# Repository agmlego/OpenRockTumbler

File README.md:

OpenRockTumbler
---------------

This project aims to be a drop-in replacement controller for common rock tumblers such as the KoolStone C1 Pro.

# Goals

* ESPHome-compatible controller for potential integration with Home Assistant
* Timer:
  * More than 9-day limit
  * Resume tumbling after power loss if time remaining
  * Periodic stir operation after timer end to prevent grit from settling
* Hall effect rotation sensor:
  * Detect if drum is actually turning
    * Alerts if belt breaks
  * Constant speed control

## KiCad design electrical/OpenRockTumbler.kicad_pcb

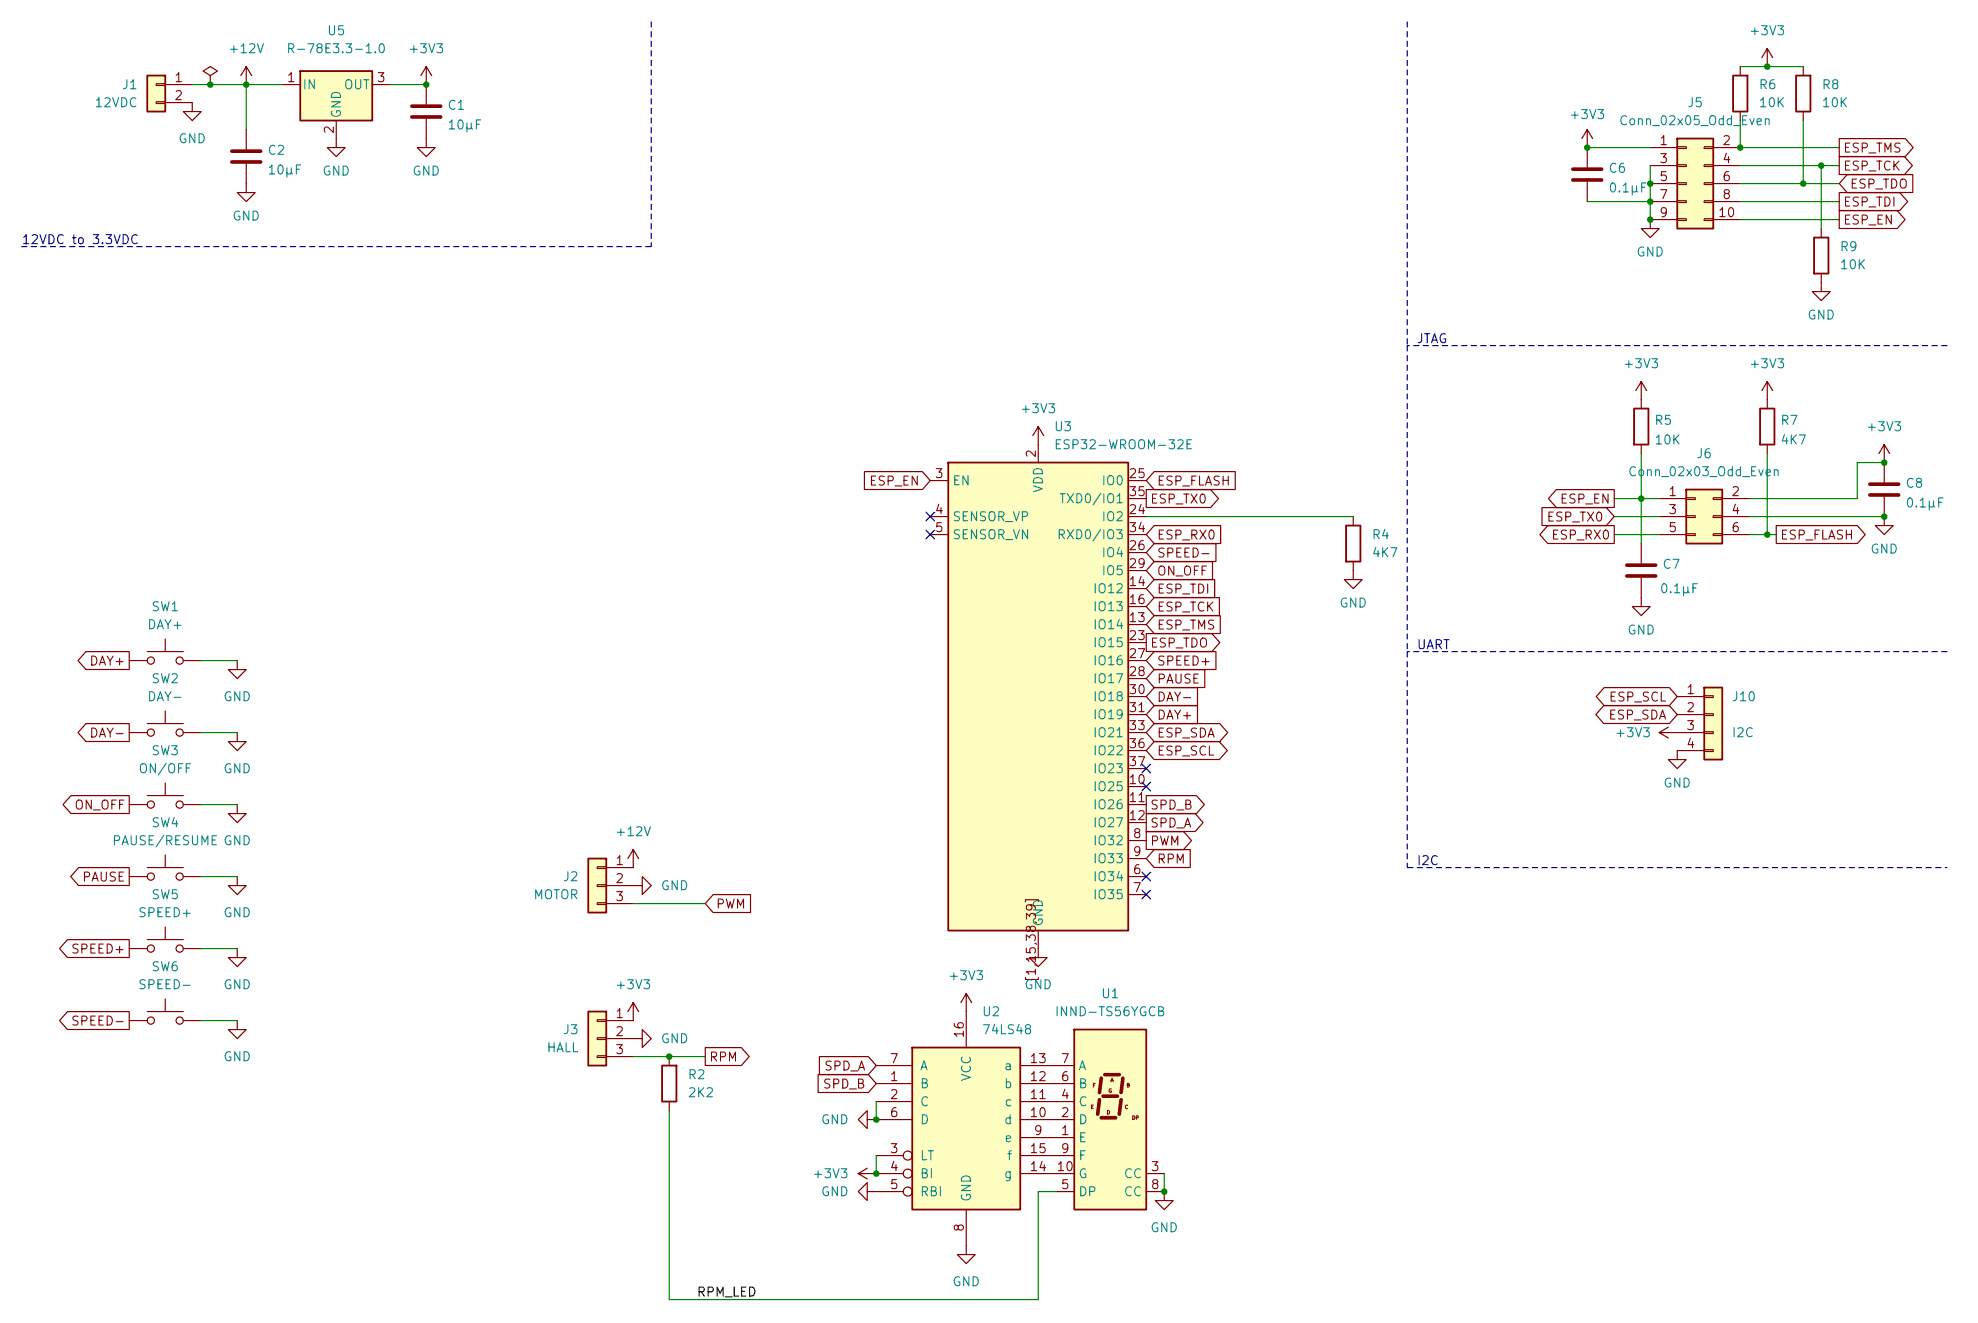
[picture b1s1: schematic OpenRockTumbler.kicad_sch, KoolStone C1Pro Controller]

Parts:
C1, C2: 10µF; CP_Elec_4x4.5
C6, C7, C8: 0.1µF; C_0603_1608Metric
J1: 12VDC; JST_PH_S2B-PH-K_1x02_P2.00mm_Horizontal
J2: MOTOR; JST_PH_S3B-PH-K_1x03_P2.00mm_Horizontal
J3: HALL; JST_PH_S3B-PH-K_1x03_P2.00mm_Horizontal
J5: Conn_02x05_Odd_Even; Tag-Connect_TC2050-IDC-NL_2x05_P1.27mm_Vertical
J6: Conn_02x03_Odd_Even; Tag-Connect_TC2030-IDC-NL_2x03_P1.27mm_Vertical
J10: I2C; JST_PH_S4B-PH-K_1x04_P2.00mm_Horizontal
R2: 2K2; R_0603_1608Metric
R4, R7: 4K7; R_0603_1608Metric
R5, R6, R8, R9: 10K; R_0603_1608Metric
SW1: DAY+; SW_PUSH_6mm
SW2: DAY-; SW_PUSH_6mm
SW3: ON/OFF; SW_PUSH_6mm
SW4: PAUSE/RESUME; SW_PUSH_6mm
SW5: SPEED+; SW_PUSH_6mm
SW6: SPEED-; SW_PUSH_6mm
U1: INND-TS56YGCB; D1X8K
U2: 74LS48; SOIC-16_3.9x9.9mm_P1.27mm
U3: ESP32-WROOM-32E
U5: R-78E3.3-1.0; Converter_DCDC_RECOM_R-78E-0.5_THT

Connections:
+3V3: C1.1, C6.1, C8.1, J3.1, J5.1, J6.2, J10.3, R5.1, R6.2, R7.1, R8.2, U2.3 (LT), U2.4 (BI), U2.16 (VCC), U3.2 (VDD), U5.3 (OUT)
+12V: C2.1, J1.1, J2.1, U5.1 (IN)
/RPM_LED: R2.1, U1.5 (DP)
DAY+: SW1.1, U3.31 (IO19)
DAY-: SW2.1, U3.30 (IO18)
ESP_EN: C7.1, J5.10, J6.1, R5.2, U3.3 (EN)
ESP_FLASH: J6.6, R7.2, U3.25 (IO0)
ESP_RX0: J6.5, U3.34 (RXD0/IO3)
ESP_SCL: J10.1, U3.36 (IO22)
ESP_SDA: J10.2, U3.33 (IO21)
ESP_TCK: J5.4, R9.1, U3.16 (IO13)
ESP_TDI: J5.8, U3.14 (IO12)
ESP_TDO: J5.6, R8.1, U3.23 (IO15)
ESP_TMS: J5.2, R6.1, U3.13 (IO14)
ESP_TX0: J6.3, U3.35 (TXD0/IO1)
GND: C1.2, C2.2, C6.2, C7.2, C8.2, J1.2, J2.2, J3.2, J5.3, J5.5, J5.7, J5.9, J6.4, J10.4, R4.2, R9.2, SW1.2, SW2.2, SW3.2, SW4.2, SW5.2, SW6.2, U1.3 (CC), U1.8 (CC), U2.2 (C), U2.5 (RBI), U2.6 (D), U2.8 (GND), U3.1 (GND), U3.15 (GND), U3.38 (GND), U3.39 (GND), U3.[1,15,38,39] (GND), U5.2 (GND)
unnamed: U1.7 (A), U2.13 (a)
unnamed: U1.6 (B), U2.12 (b)
unnamed: U1.4 (C), U2.11 (c)
unnamed: U1.2 (D), U2.10 (d)
unnamed: U1.1 (E), U2.9 (e)
unnamed: U1.9 (F), U2.15 (f)
unnamed: U1.10 (G), U2.14 (g)
unnamed: R4.1, U3.24 (IO2)
ON_OFF: SW3.1, U3.29 (IO5)
PAUSE: SW4.1, U3.28 (IO17)
PWM: J2.3, U3.8 (IO32)
RPM: J3.3, R2.2, U3.9 (IO33)
SPD_A: U2.7 (A), U3.12 (IO27)
SPD_B: U2.1 (B), U3.11 (IO26)
SPEED+: SW5.1, U3.27 (IO16)
SPEED-: SW6.1, U3.26 (IO4)

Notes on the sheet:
I2C
JTAG
UART
12VDC to 3.3VDC

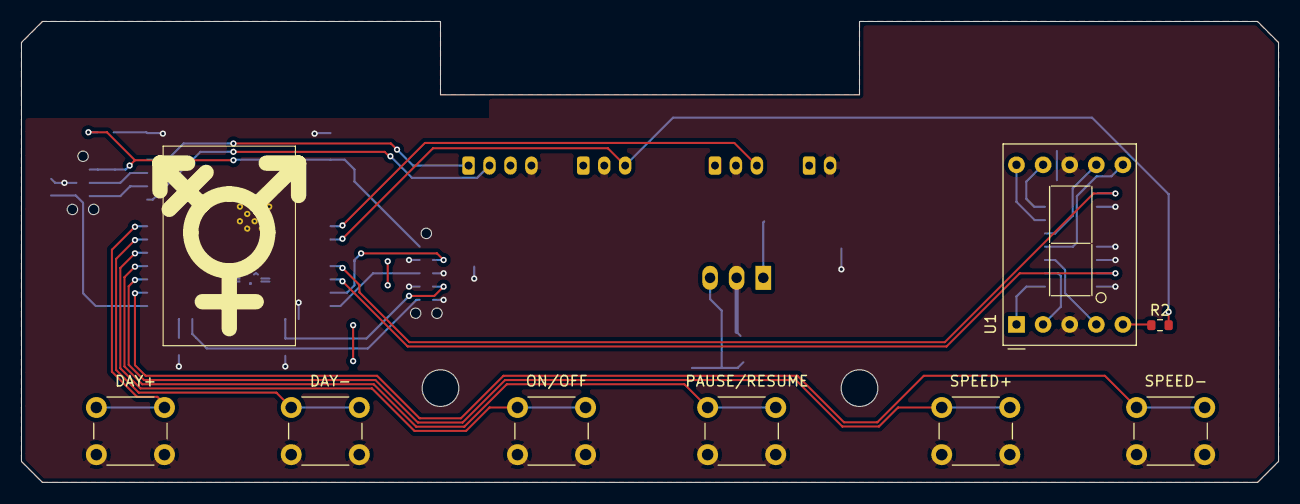
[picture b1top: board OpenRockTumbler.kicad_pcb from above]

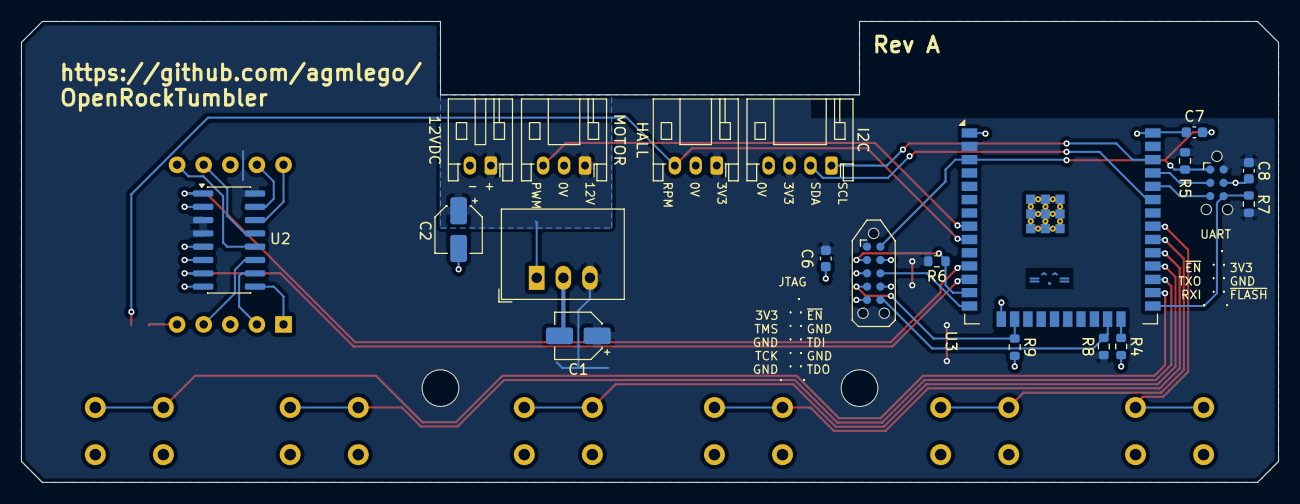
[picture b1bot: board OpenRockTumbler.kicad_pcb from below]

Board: 2 copper layers, 120.0 x 44.0 mm, 28 parts (20 on the bottom side), 32 nets.

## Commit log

2026-06-26 Initial commit with first pass routing on C1Pro board
2026-06-26 Update pcb_image.yaml for newer action API
2026-06-26 Updated silk
2026-06-26 Updated DRC for OSHPark
2026-06-28 Replaced 5V regulator and 3V3 regulator with single 3V3 regulator
2026-06-30 Added sample screens as layers for the OLED screen
